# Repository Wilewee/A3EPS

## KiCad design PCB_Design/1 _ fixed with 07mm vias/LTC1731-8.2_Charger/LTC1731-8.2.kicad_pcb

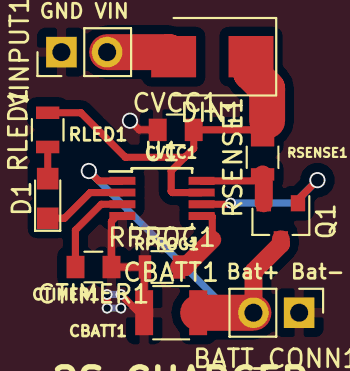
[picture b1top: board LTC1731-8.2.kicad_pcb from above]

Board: 2 copper layers, 12 parts (0 on the bottom side), 10 nets.

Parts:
BATT_CONN1: CONN_OUT; Socket_Strip_Straight_1x02_Pitch2.54mm
CBATT1: 10U; C_1210
CTIMER1: 0.1UF; C_0805
CVCC1: 1U; C_0805
D1: LED; LED_0805
DIN1: D_Schottky; D_SMB_Standard
Q1: Q_PMOS_GSD; SOT-23
RLED1: 2K; R_0805
RPROG1: 19.6K; R_0805
RSENSE1: 0.2; R_0805
U1: LTC-1731; MSOP-8_3x3mm_Pitch0.65mm
VINPUT1: CONN_IN; Socket_Strip_Straight_1x02_Pitch2.54mm

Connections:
/BATT+: BATT_CONN1.2, CBATT1.2, Q1.3, U1.1
GND: BATT_CONN1.1, CBATT1.1, CTIMER1.1, CVCC1.1, RPROG1.1, U1.4, VINPUT1.1
unnamed: CTIMER1.2, U1.3
unnamed: CVCC1.2, DIN1.1, RLED1.2, RSENSE1.2, U1.7
unnamed: D1.1, U1.2
unnamed: D1.2, RLED1.1
unnamed: DIN1.2, VINPUT1.2
unnamed: Q1.1, U1.6
unnamed: Q1.2, RSENSE1.1, U1.8
unnamed: RPROG1.2, U1.5
